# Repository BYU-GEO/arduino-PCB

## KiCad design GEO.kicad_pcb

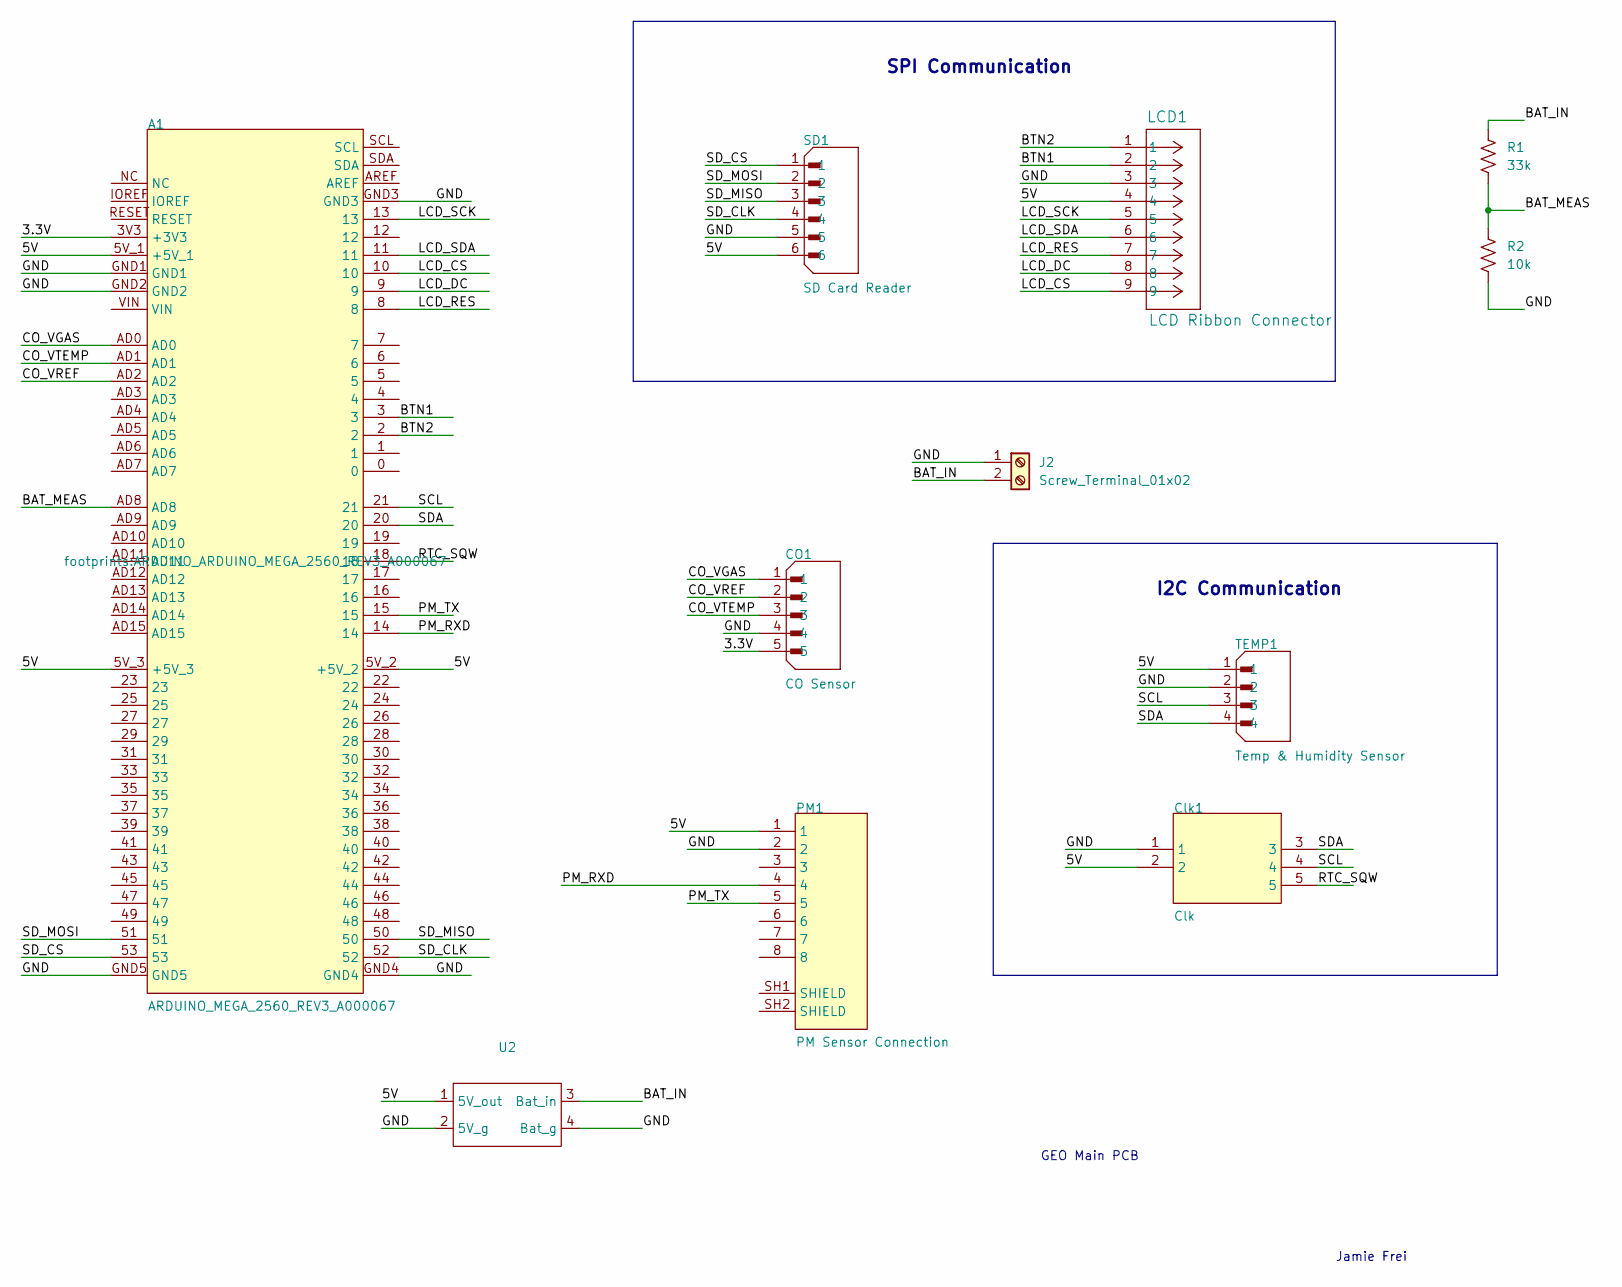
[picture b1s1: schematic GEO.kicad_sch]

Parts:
A1: ARDUINO_MEGA_2560_REV3_A000067; ARDUINO_ARDUINO_MEGA_2560_REV3_A000067
CO1: CO Sensor; JST_B5B-XH-A
Clk1: Clk; TE_5-146280-5
J2: Screw_Terminal_01x02; TerminalBlock_MaiXu_MX126-5.0-02P_1x02_P5.00mm
LCD1: LCD Ribbon Connector; TE_84952-9_1x09-1MP_P1.0mm_Horizontal
PM1: PM Sensor Connection; JST_SM08B-GHS-TB(LF)(SN); DIGI-KEY_PART_NUMBER 455-1570-1-ND
R1: 33k; R_Axial_DIN0309_L9.0mm_D3.2mm_P12.70mm_Horizontal
R2: 10k; R_Axial_DIN0309_L9.0mm_D3.2mm_P12.70mm_Horizontal
SD1: SD Card Reader; JST_B6B-XH-A(LF)(SN)
TEMP1: Temp & Humidity Sensor; JST_B4B-XH-A(LF)(SN)
U2: DFR1015 Buck_Converter

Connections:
/3.3V: A1.3V3 (+3V3), CO1.5
/5V: A1.5V_1 (+5V_1), A1.5V_2 (+5V_2), A1.5V_3 (+5V_3), Clk1.2, LCD1.4, PM1.1, SD1.6, TEMP1.1, U2.1 (5V_out)
/BAT_IN: J2.2, R1.2, U2.3 (Bat_in)
/BAT_MEAS: A1.AD8, R1.1, R2.2
/BTN1: A1.3, LCD1.2
/BTN2: A1.2, LCD1.1
/CO_VGAS: A1.AD0, CO1.1
/CO_VREF: A1.AD2, CO1.2
/CO_VTEMP: A1.AD1, CO1.3
/GND: A1.GND1, A1.GND2, A1.GND3, A1.GND4, A1.GND5, CO1.4, Clk1.1, J2.1, LCD1.3, PM1.2, R2.1, SD1.5, TEMP1.2, U2.2 (5V_g), U2.4 (Bat_g)
/LCD_CS: A1.10, LCD1.9
/LCD_DC: A1.9, LCD1.8
/LCD_RES: A1.8, LCD1.7
/LCD_SCK: A1.13, LCD1.5
/LCD_SDA: A1.11, LCD1.6
/PM_RXD: A1.14, PM1.4
/PM_TX: A1.15, PM1.5
/RTC_SQW: A1.18, Clk1.5
/SCL: A1.21, Clk1.4, TEMP1.3
/SDA: A1.20, Clk1.3, TEMP1.4
/SD_CLK: A1.52, SD1.4
/SD_CS: A1.53, SD1.1
/SD_MISO: A1.50, SD1.3
/SD_MOSI: A1.51, SD1.2

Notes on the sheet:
Jamie Frei
GEO Main PCB
I2C Communication
SPI Communication

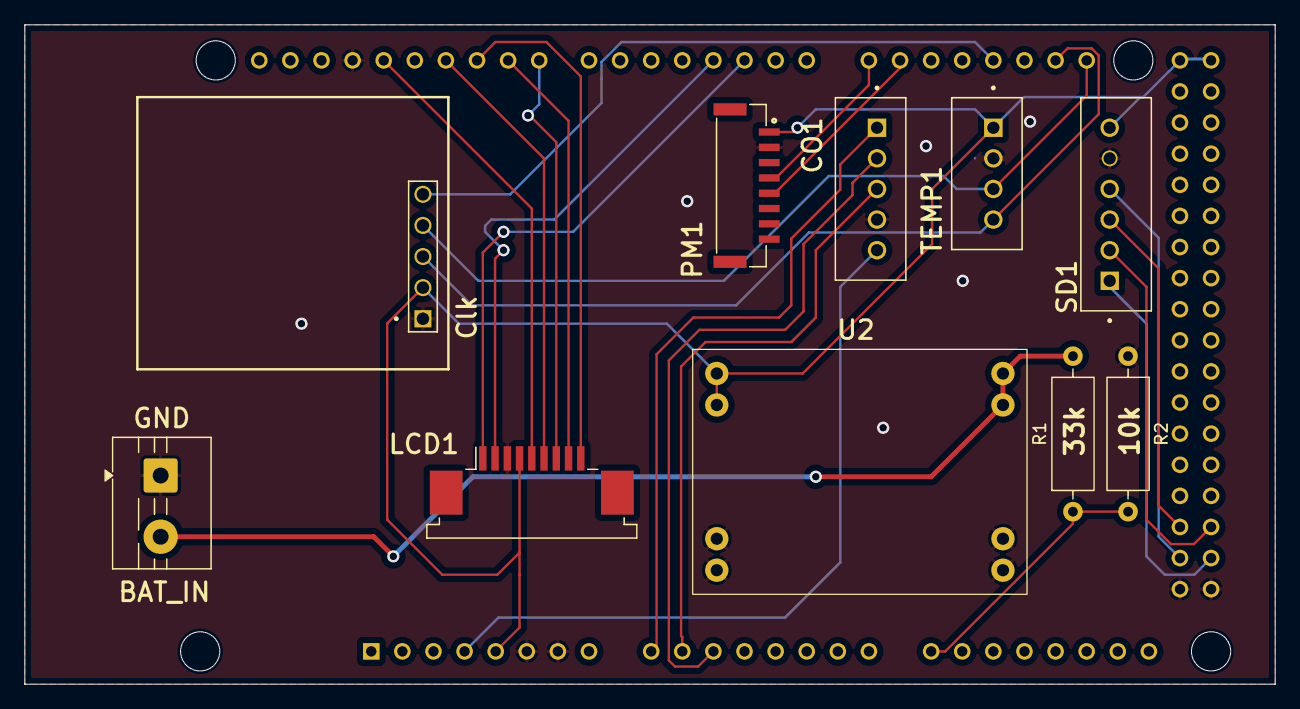
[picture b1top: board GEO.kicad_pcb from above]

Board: 2 copper layers, 102.1 x 53.8 mm, 11 parts (0 on the bottom side), 24 nets.

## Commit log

2026-02-25 init commit
2026-02-25 changed two pin header
2026-03-04 flip buck converter and add screw terminal, gen gerber files
2026-03-12 removed Vref circuitry from CO sensor and wired Vref to pin A2
2026-04-02 gerber 03-24-26, add VRef pin
2026-06-19 cleaned up the schematic
